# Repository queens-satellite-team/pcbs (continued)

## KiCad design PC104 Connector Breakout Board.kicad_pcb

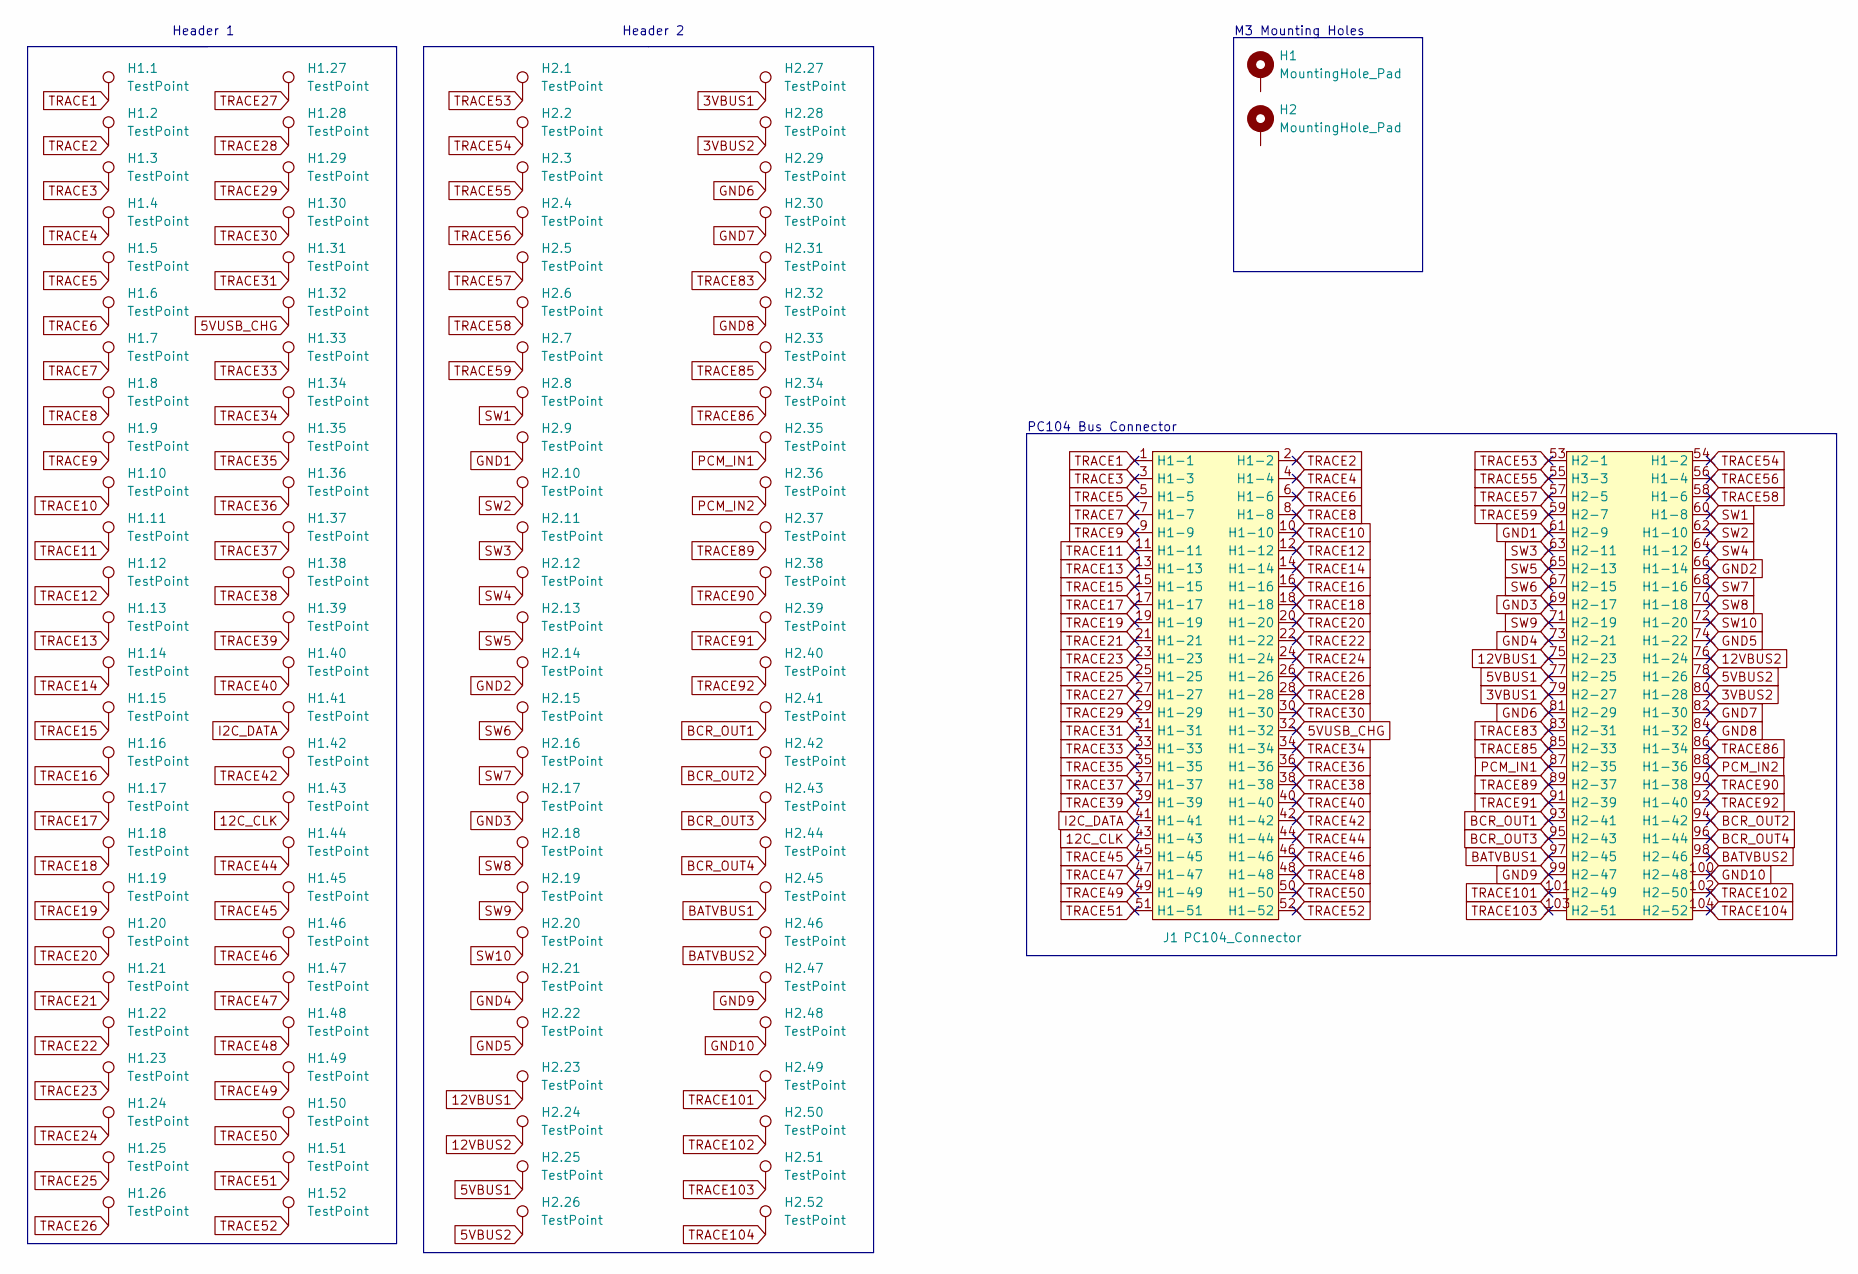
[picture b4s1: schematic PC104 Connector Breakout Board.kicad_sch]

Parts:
H1, H2: MountingHole_Pad; MountingHole_3.2mm_M3_Pad_TopBottom
H1.1, H1.2, H1.3, H1.4, H1.5, H1.6, H1.7, H1.8, H1.9, H1.10, H1.11, H1.12, H1.13, H1.14, H1.15, H1.16, H1.17, H1.18, H1.19, H1.20, H1.21, H1.22, H1.23, H1.24, H1.25, H1.26, H1.27, H1.28, H1.29, H1.30, H1.31, H1.32, H1.33, H1.34, H1.35, H1.36, H1.37, H1.38, H1.39, H1.40, H1.41, H1.42, H1.43, H1.44, H1.45, H1.46, H1.47, H1.48, H1.49, H1.50, H1.51, H1.52, H2.1, H2.2, H2.3, H2.4, H2.5, H2.6, H2.7, H2.8, H2.9, H2.10, H2.11, H2.12, H2.13, H2.14, H2.15, H2.16, H2.17, H2.18, H2.19, H2.20, H2.21, H2.22, H2.23, H2.24, H2.25, H2.26, H2.27, H2.28, H2.29, H2.30, H2.31, H2.32, H2.33, H2.34, H2.35, H2.36, H2.37, H2.38, H2.39, H2.40, H2.41, H2.42, H2.43, H2.44, H2.45, H2.46, H2.47, H2.48, H2.49, H2.50, H2.51, H2.52: TestPoint; TestPoint_Keystone_5000-5004_Miniature
J1: PC104_Connector; pc104-connector

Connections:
3VBUS1: H2.27.1, J1.79 (H2-27)
3VBUS2: H2.28.1, J1.80 (H1-28)
5VBUS1: H2.25.1, J1.77 (H2-25)
5VBUS2: H2.26.1, J1.78 (H1-26)
5VUSB_CHG: H1.32.1, J1.32 (H1-32)
12C_CLK: H1.43.1, J1.43 (H1-43)
12VBUS1: H2.23.1, J1.75 (H2-23)
12VBUS2: H2.24.1, J1.76 (H1-24)
BATVBUS1: H2.45.1, J1.97 (H2-45)
BATVBUS2: H2.46.1, J1.98 (H2-46)
BCR_OUT1: H2.41.1, J1.93 (H2-41)
BCR_OUT2: H2.42.1, J1.94 (H1-42)
BCR_OUT3: H2.43.1, J1.95 (H2-43)
BCR_OUT4: H2.44.1, J1.96 (H1-44)
GND1: H2.9.1, J1.61 (H2-9)
GND2: H2.14.1, J1.66 (H1-14)
GND3: H2.17.1, J1.69 (H2-17)
GND4: H2.21.1, J1.73 (H2-21)
GND5: H2.22.1, J1.74 (H1-22)
GND6: H2.29.1, J1.81 (H2-29)
GND7: H2.30.1, J1.82 (H1-30)
GND8: H2.32.1, J1.84 (H1-32)
GND9: H2.47.1, J1.99 (H2-47)
GND10: H2.48.1, J1.100 (H2-48)
I2C_DATA: H1.41.1, J1.41 (H1-41)
PCM_IN1: H2.35.1, J1.87 (H2-35)
PCM_IN2: H2.36.1, J1.88 (H1-36)
SW1: H2.8.1, J1.60 (H1-8)
SW2: H2.10.1, J1.62 (H1-10)
SW3: H2.11.1, J1.63 (H2-11)
SW4: H2.12.1, J1.64 (H1-12)
SW5: H2.13.1, J1.65 (H2-13)
SW6: H2.15.1, J1.67 (H2-15)
SW7: H2.16.1, J1.68 (H1-16)
SW8: H2.18.1, J1.70 (H1-18)
SW9: H2.19.1, J1.71 (H2-19)
SW10: H2.20.1, J1.72 (H1-20)
TRACE1: H1.1.1, J1.1 (H1-1)
TRACE2: H1.2.1, J1.2 (H1-2)
TRACE3: H1.3.1, J1.3 (H1-3)
TRACE4: H1.4.1, J1.4 (H1-4)
TRACE5: H1.5.1, J1.5 (H1-5)
TRACE6: H1.6.1, J1.6 (H1-6)
TRACE7: H1.7.1, J1.7 (H1-7)
TRACE8: H1.8.1, J1.8 (H1-8)
TRACE9: H1.9.1, J1.9 (H1-9)
TRACE10: H1.10.1, J1.10 (H1-10)
TRACE11: H1.11.1, J1.11 (H1-11)
TRACE12: H1.12.1, J1.12 (H1-12)
TRACE13: H1.13.1, J1.13 (H1-13)
TRACE14: H1.14.1, J1.14 (H1-14)
TRACE15: H1.15.1, J1.15 (H1-15)
TRACE16: H1.16.1, J1.16 (H1-16)
TRACE17: H1.17.1, J1.17 (H1-17)
TRACE18: H1.18.1, J1.18 (H1-18)
TRACE19: H1.19.1, J1.19 (H1-19)
TRACE20: H1.20.1, J1.20 (H1-20)
TRACE21: H1.21.1, J1.21 (H1-21)
TRACE22: H1.22.1, J1.22 (H1-22)
TRACE23: H1.23.1, J1.23 (H1-23)
TRACE24: H1.24.1, J1.24 (H1-24)
TRACE25: H1.25.1, J1.25 (H1-25)
TRACE26: H1.26.1, J1.26 (H1-26)
TRACE27: H1.27.1, J1.27 (H1-27)
TRACE28: H1.28.1, J1.28 (H1-28)
TRACE29: H1.29.1, J1.29 (H1-29)
TRACE30: H1.30.1, J1.30 (H1-30)
TRACE31: H1.31.1, J1.31 (H1-31)
TRACE33: H1.33.1, J1.33 (H1-33)
TRACE34: H1.34.1, J1.34 (H1-34)
TRACE35: H1.35.1, J1.35 (H1-35)
TRACE36: H1.36.1, J1.36 (H1-36)
TRACE37: H1.37.1, J1.37 (H1-37)
TRACE38: H1.38.1, J1.38 (H1-38)
TRACE39: H1.39.1, J1.39 (H1-39)
TRACE40: H1.40.1, J1.40 (H1-40)
TRACE42: H1.42.1, J1.42 (H1-42)
TRACE44: H1.44.1, J1.44 (H1-44)
TRACE45: H1.45.1, J1.45 (H1-45)
TRACE46: H1.46.1, J1.46 (H1-46)
TRACE47: H1.47.1, J1.47 (H1-47)
TRACE48: H1.48.1, J1.48 (H1-48)
TRACE49: H1.49.1, J1.49 (H1-49)
TRACE50: H1.50.1, J1.50 (H1-50)
TRACE51: H1.51.1, J1.51 (H1-51)
TRACE52: H1.52.1, J1.52 (H1-52)
TRACE53: H2.1.1, J1.53 (H2-1)
TRACE54: H2.2.1, J1.54 (H1-2)
TRACE55: H2.3.1, J1.55 (H3-3)
TRACE56: H2.4.1, J1.56 (H1-4)
TRACE57: H2.5.1, J1.57 (H2-5)
TRACE58: H2.6.1, J1.58 (H1-6)
TRACE59: H2.7.1, J1.59 (H2-7)
TRACE83: H2.31.1, J1.83 (H2-31)
TRACE85: H2.33.1, J1.85 (H2-33)
TRACE86: H2.34.1, J1.86 (H1-34)
TRACE89: H2.37.1, J1.89 (H2-37)
TRACE90: H2.38.1, J1.90 (H1-38)
TRACE91: H2.39.1, J1.91 (H2-39)
TRACE92: H2.40.1, J1.92 (H1-40)
TRACE101: H2.49.1, J1.101 (H2-49)
TRACE102: H2.50.1, J1.102 (H2-50)
TRACE103: H2.51.1, J1.103 (H2-51)
TRACE104: H2.52.1, J1.104 (H2-52)

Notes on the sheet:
M3 Mounting Holes
Header 2
Header 1
PC104 Bus Connector

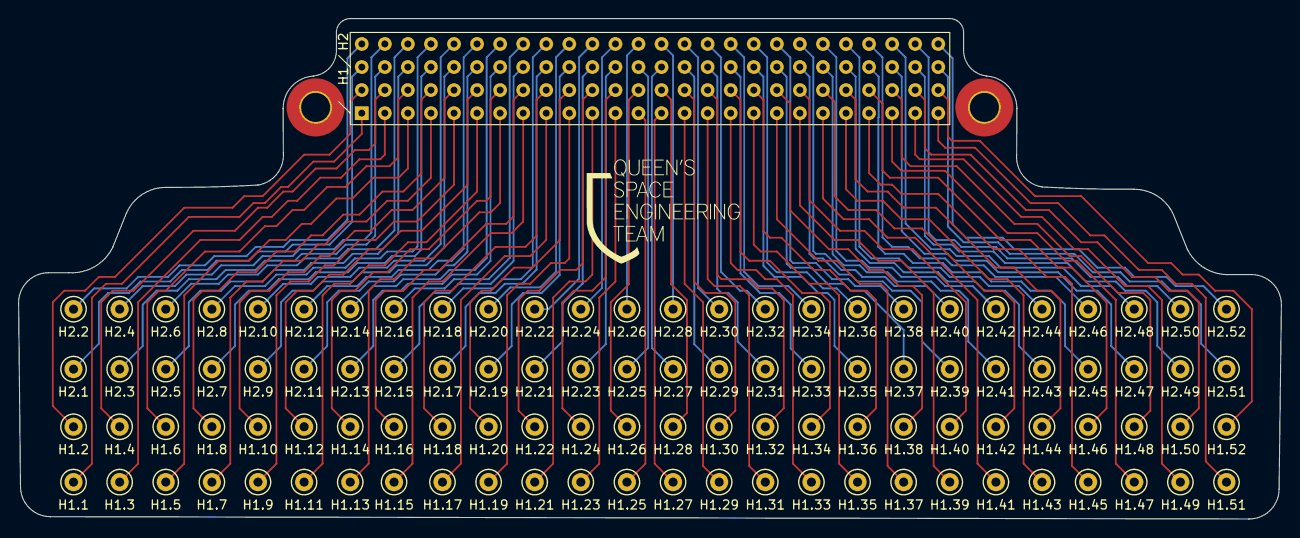
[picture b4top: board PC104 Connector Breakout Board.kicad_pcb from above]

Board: 2 copper layers, 139.1 x 55.1 mm, 107 parts (0 on the bottom side), 104 nets.
